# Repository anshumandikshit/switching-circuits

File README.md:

# switching-circuits
the pcb design of the switching circuit by using opto coupler and mosfets

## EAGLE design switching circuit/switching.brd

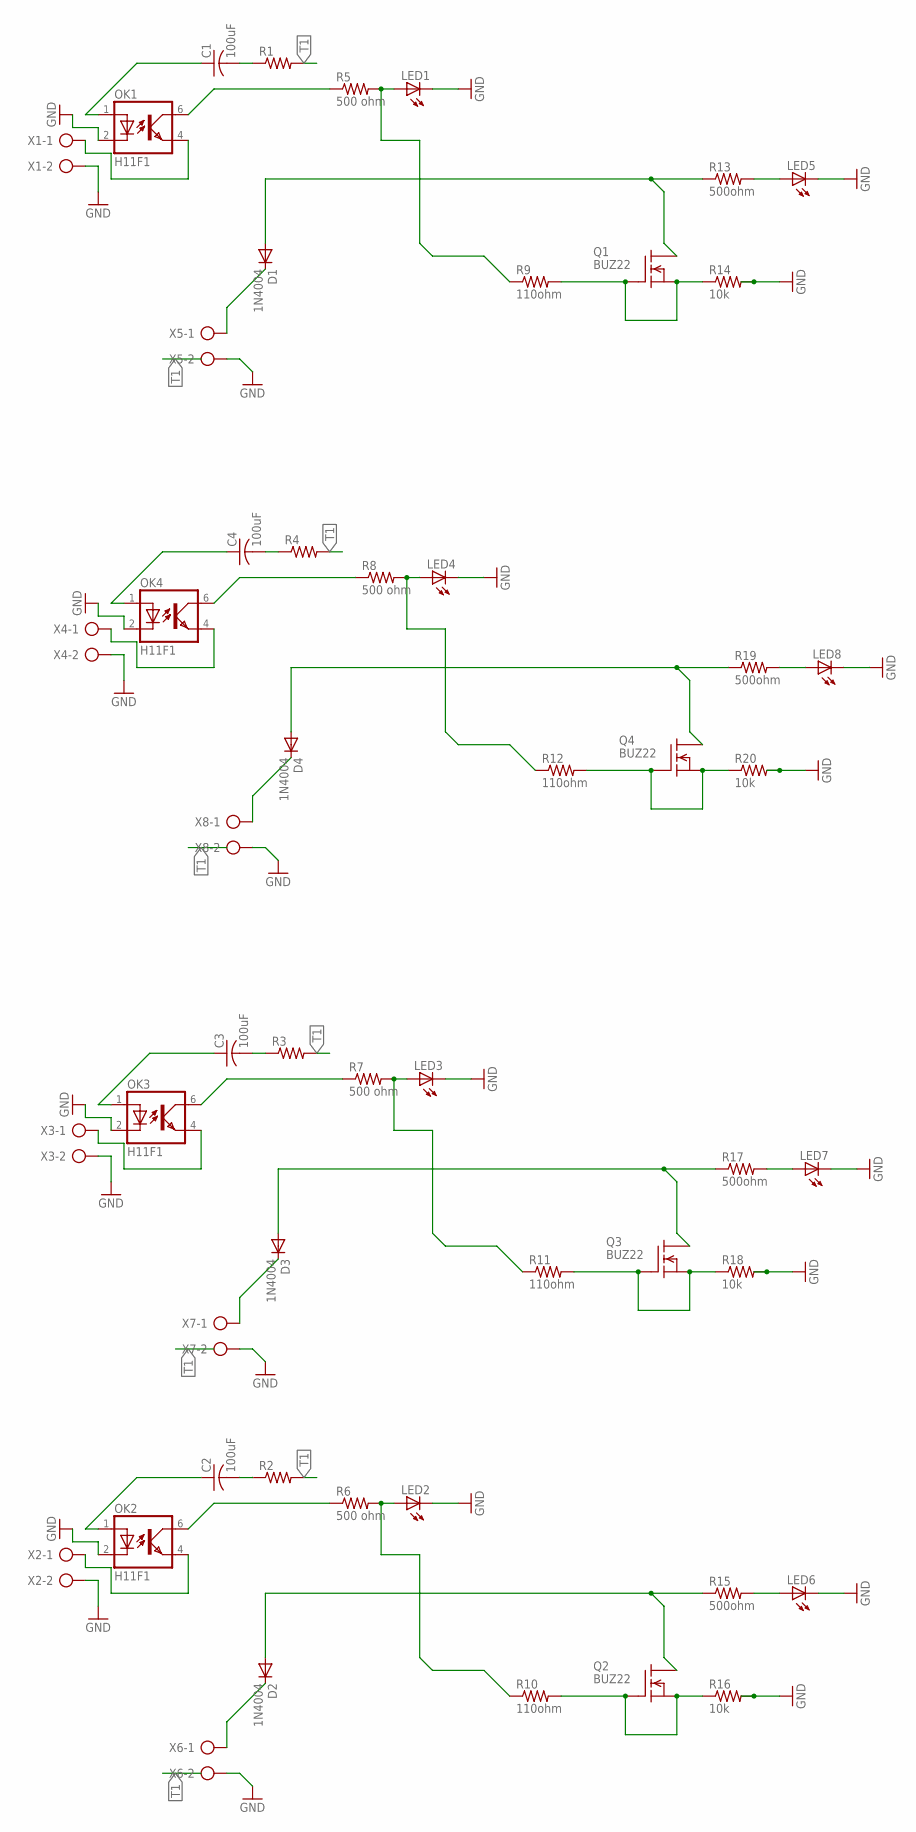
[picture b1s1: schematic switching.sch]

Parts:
C1, C2, C3, C4: 100uF; C025-024X044; MPN 08055C104KAT2A
D1, D2, D3, D4: 1N4004; DO41-10; MPN 1N4004G
LED1, LED2, LED3, LED4, LED5, LED6, LED7, LED8: LED3MM; MPN SSL-LX3044LID.
OK1, OK2, OK3, OK4: H11F1; DIL05
Q1, Q2, Q3, Q4: BUZ22; TO220; MPN IRF1310NPBF
R1, R2, R3, R4: R-US_0204/7; 0204/7; MPN CC0402KRX7R7BB104
R5, R6, R7, R8: 500 ohm; 0204/7; MPN CC0402JRNPO9BN101
R9, R10, R11, R12: 110ohm; 0204/7; MPN ERJ3GEYJ111V
R13, R15, R17, R19: 500ohm; 0204/7; MPN CC0402JRNPO9BN101
R14, R16, R18, R20: 10k; 0204/7; MPN CRCW040210K0FKED
X1, X2, X3, X4, X5, X6, X7, X8: AK500/2

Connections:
GND: LED1.K (C), LED2.K (C), LED3.K (C), LED4.K (C), LED5.K (C), LED6.K (C), LED7.K (C), LED8.K (C), OK1.2 (C), OK2.2 (C), OK3.2 (C), OK4.2 (C), R14.2, R16.2, R18.2, R20.2, X1.2, X2.2, X3.2, X4.2, X5.2, X6.2, X7.2, X8.2
unnamed: OK3.4 (EMIT), X3.1
unnamed: OK3.6 (COL), R7.1
unnamed: C3.1, OK3.1 (A)
unnamed: LED3.A, R7.2, R11.1
unnamed: Q3.1 (G), Q3.3 (S), R11.2, R18.1
unnamed: D3.A, Q3.2 (D), R17.1
unnamed: LED7.A, R17.2
unnamed: D3.C, X7.1
unnamed: OK2.4 (EMIT), X2.1
unnamed: C3.2, R3.1
unnamed: C2.1, OK2.1 (A)
unnamed: OK2.6 (COL), R6.1
unnamed: LED2.A, R6.2, R10.1
unnamed: Q2.1 (G), Q2.3 (S), R10.2, R16.1
unnamed: D2.A, Q2.2 (D), R15.1
unnamed: LED6.A, R15.2
unnamed: D2.C, X6.1
unnamed: C2.2, R2.1
unnamed: OK4.4 (EMIT), X4.1
unnamed: C4.1, OK4.1 (A)
unnamed: OK4.6 (COL), R8.1
unnamed: LED4.A, R8.2, R12.1
unnamed: Q4.1 (G), Q4.3 (S), R12.2, R20.1
unnamed: D4.A, Q4.2 (D), R19.1
unnamed: LED8.A, R19.2
unnamed: D4.C, X8.1
unnamed: C4.2, R4.1
unnamed: OK1.4 (EMIT), X1.1
unnamed: C1.1, OK1.1 (A)
unnamed: OK1.6 (COL), R5.1
unnamed: LED1.A, R5.2, R9.1
unnamed: Q1.1 (G), Q1.3 (S), R9.2, R14.1
unnamed: D1.A, Q1.2 (D), R13.1
unnamed: LED5.A, R13.2
unnamed: D1.C, X5.1
unnamed: C1.2, R1.1
T1: R1.2, R2.2, R3.2, R4.2

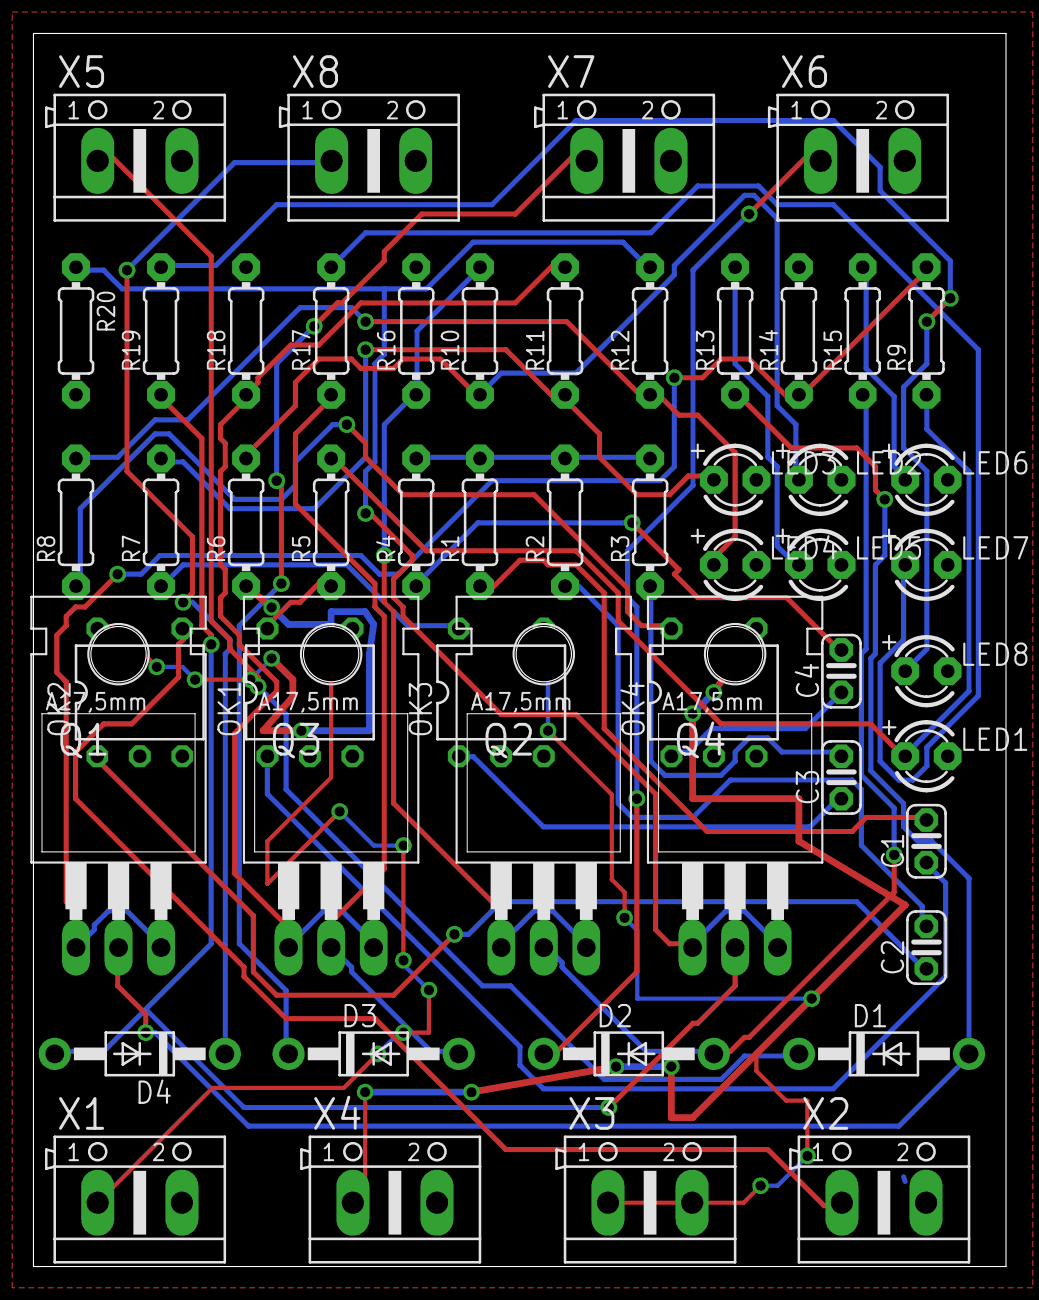
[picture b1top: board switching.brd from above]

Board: 2 copper layers, 58.1 x 73.7 mm, 52 parts (0 on the bottom side), 38 nets.
